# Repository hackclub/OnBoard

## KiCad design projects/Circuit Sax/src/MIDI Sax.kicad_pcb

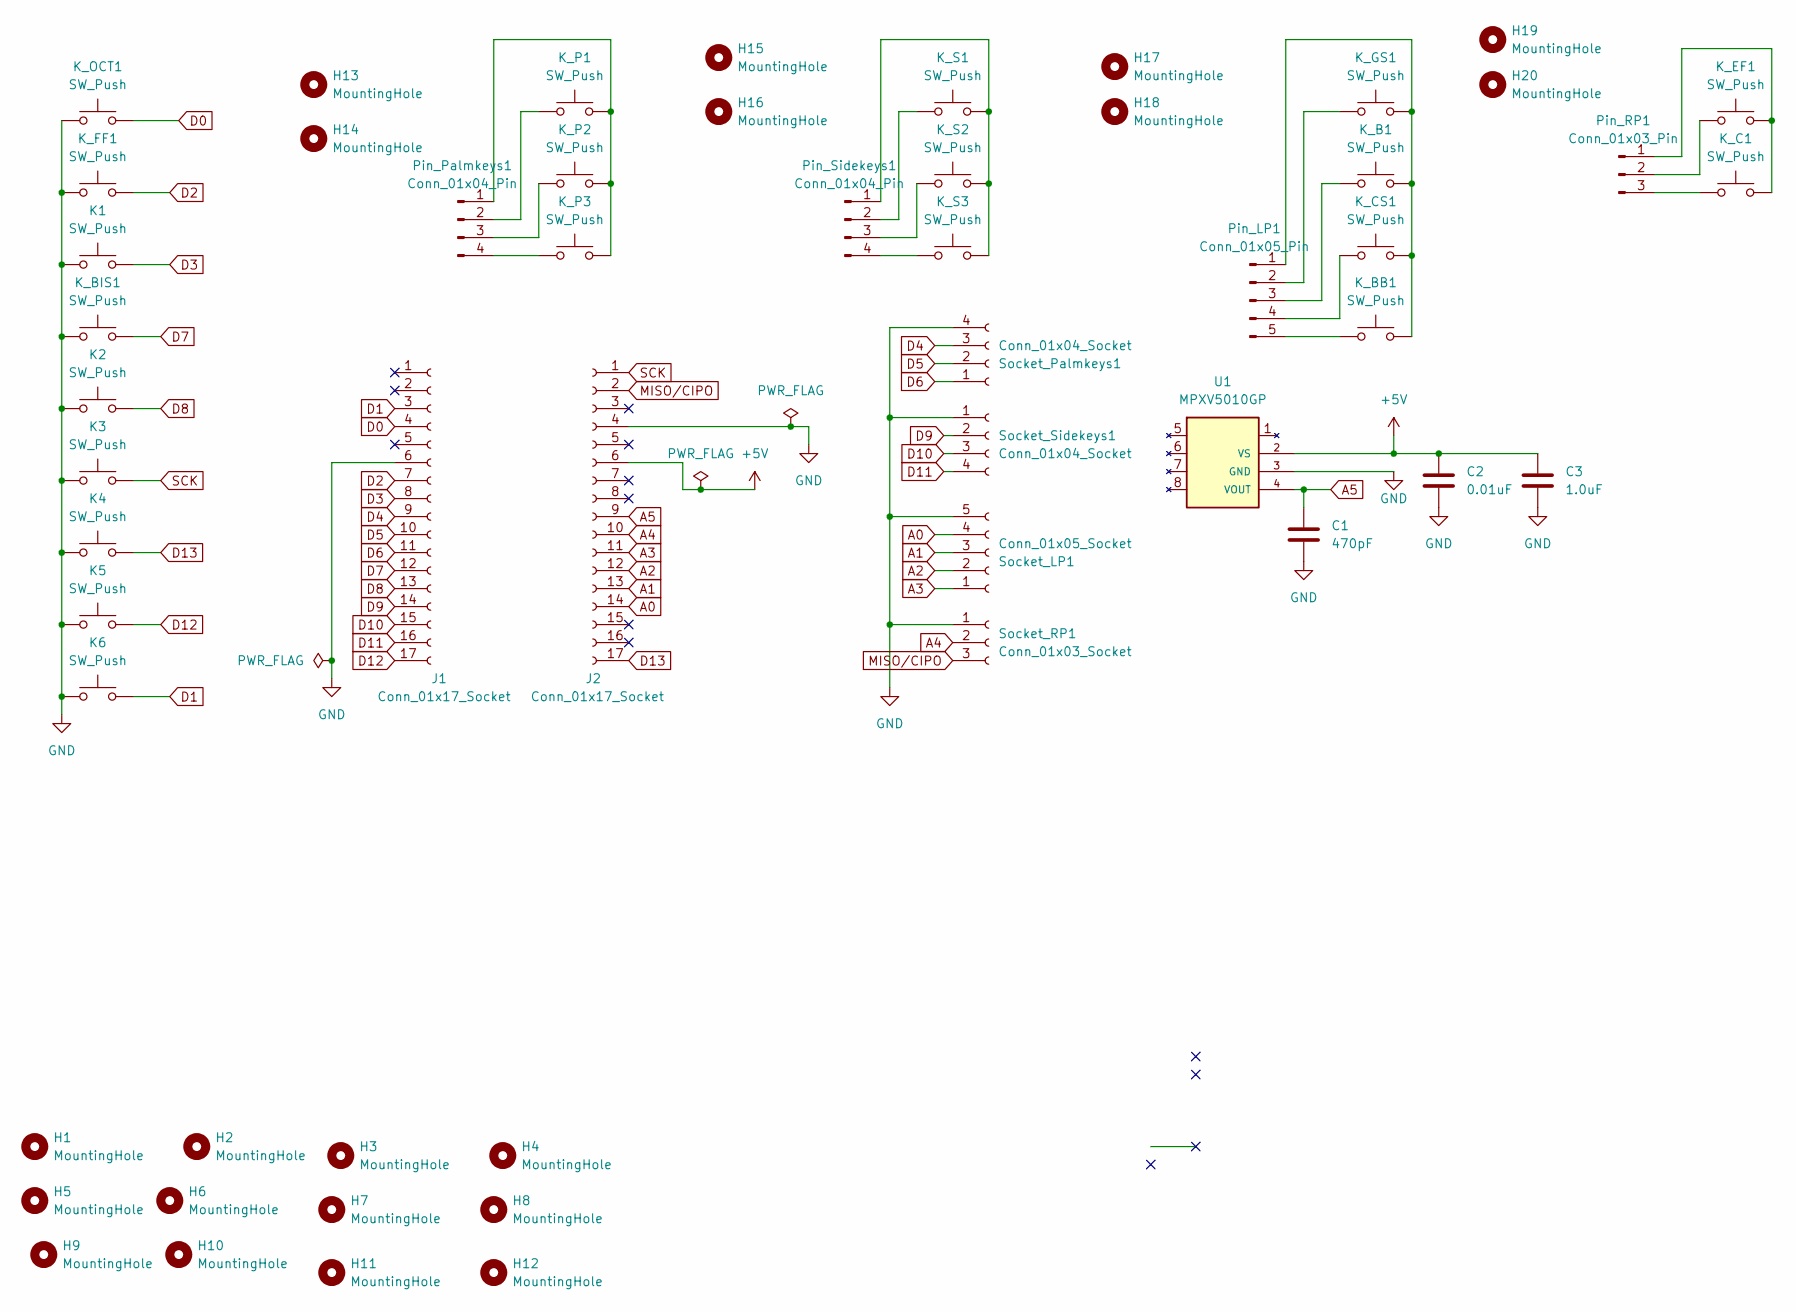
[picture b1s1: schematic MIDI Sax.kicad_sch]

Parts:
C1: 470pF; C_1206_3216Metric
C2: 0.01uF; C_1206_3216Metric
C3: 1.0uF; C_1206_3216Metric
H1, H2, H3, H4, H5, H6, H9, H10, H11, H12, H13, H14, H17, H18: MountingHole; MountingHole_2.85mm
H7, H8, H15, H16, H19, H20: MountingHole; MountingHole_3.3mm
J1, J2: Conn_01x17_Socket; PinSocket_1x17_P2.54mm_Vertical
K1, K2, K3, K4, K5, K6: SW_Push; SW_Cherry_MX_PCB
K_B1: SW_Push; SW_Cherry_MX_PCB
K_BB1: SW_Push; SW_Cherry_MX_PCB
K_BIS1: SW_Push; SW_Cherry_MX_PCB
K_C1: SW_Push; SW_Cherry_MX_PCB
K_CS1: SW_Push; SW_Cherry_MX_PCB
K_EF1: SW_Push; SW_Cherry_MX_PCB
K_FF1: SW_Push; SW_Cherry_MX_PCB
K_GS1: SW_Push; SW_Cherry_MX_PCB
K_OCT1: SW_Push; SW_Cherry_MX_PCB
K_P1, K_P2, K_P3: SW_Push; SW_Cherry_MX_PCB
K_S1, K_S2, K_S3: SW_Push; SW_Cherry_MX_PCB
Pin_LP1: Conn_01x05_Pin; SAMTEC_TSM-105-01-L-SH
Pin_Palmkeys1: Conn_01x04_Pin; PinHeader_1x04_P2.54mm_Vertical
Pin_RP1: Conn_01x03_Pin; CONN3_M20-8900_HRW
Pin_Sidekeys1: Conn_01x04_Pin; PinHeader_1x04_P2.54mm_Vertical
Socket_LP1: Conn_01x05_Socket; HARWIN_M20-7910542R
Socket_Palmkeys1: Conn_01x04_Socket; HARWIN_M20-7910442R
Socket_RP1: Conn_01x03_Socket; HARWIN_M20-7910342R
Socket_Sidekeys1: Conn_01x04_Socket; HARWIN_M20-7910442R
U1: MPXV5010GP; SOIC254P1821X762-8N

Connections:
+5V: C2.1, C3.1, J2.6, U1.2 (VS)
A0: J2.14, Socket_LP1.4
A1: J2.13, Socket_LP1.3
A2: J2.12, Socket_LP1.2
A3: J2.11, Socket_LP1.1
A4: J2.10, Socket_RP1.2
A5: C1.1, J2.9, U1.4 (VOUT)
D0: J1.4, K_OCT1.2
D1: J1.3, K6.2
D2: J1.7, K_FF1.2
D3: J1.8, K1.2
D4: J1.9, Socket_Palmkeys1.3
D5: J1.10, Socket_Palmkeys1.2
D6: J1.11, Socket_Palmkeys1.1
D7: J1.12, K_BIS1.2
D8: J1.13, K2.2
D9: J1.14, Socket_Sidekeys1.2
D10: J1.15, Socket_Sidekeys1.3
D11: J1.16, Socket_Sidekeys1.4
D12: J1.17, K5.2
D13: J2.17, K4.2
GND: C1.2, C2.2, C3.2, J1.6, J2.4, K1.1, K2.1, K3.1, K4.1, K5.1, K6.1, K_BIS1.1, K_FF1.1, K_OCT1.1, Socket_LP1.5, Socket_Palmkeys1.4, Socket_RP1.1, Socket_Sidekeys1.1, U1.3 (GND)
MISO/CIPO: J2.2, Socket_RP1.3
unnamed: K_B1.2, K_BB1.2, K_CS1.2, K_GS1.2, Pin_LP1.1
unnamed: K_GS1.1, Pin_LP1.2
unnamed: K_B1.1, Pin_LP1.3
unnamed: K_CS1.1, Pin_LP1.4
unnamed: K_BB1.1, Pin_LP1.5
unnamed: K_P1.2, K_P2.2, K_P3.2, Pin_Palmkeys1.1
unnamed: K_P1.1, Pin_Palmkeys1.2
unnamed: K_P2.1, Pin_Palmkeys1.3
unnamed: K_P3.1, Pin_Palmkeys1.4
unnamed: K_C1.2, K_EF1.2, Pin_RP1.1
unnamed: K_EF1.1, Pin_RP1.2
unnamed: K_C1.1, Pin_RP1.3
unnamed: K_S1.2, K_S2.2, K_S3.2, Pin_Sidekeys1.1
unnamed: K_S1.1, Pin_Sidekeys1.2
unnamed: K_S2.1, Pin_Sidekeys1.3
unnamed: K_S3.1, Pin_Sidekeys1.4
SCK: J2.1, K3.2

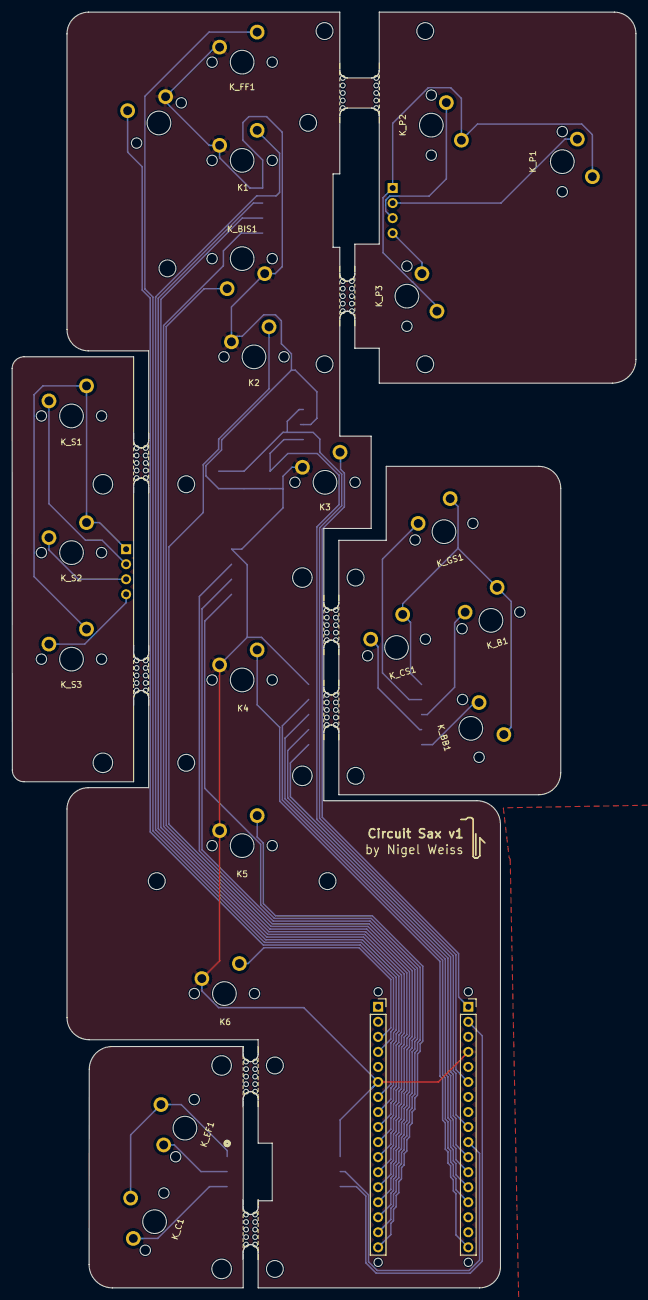
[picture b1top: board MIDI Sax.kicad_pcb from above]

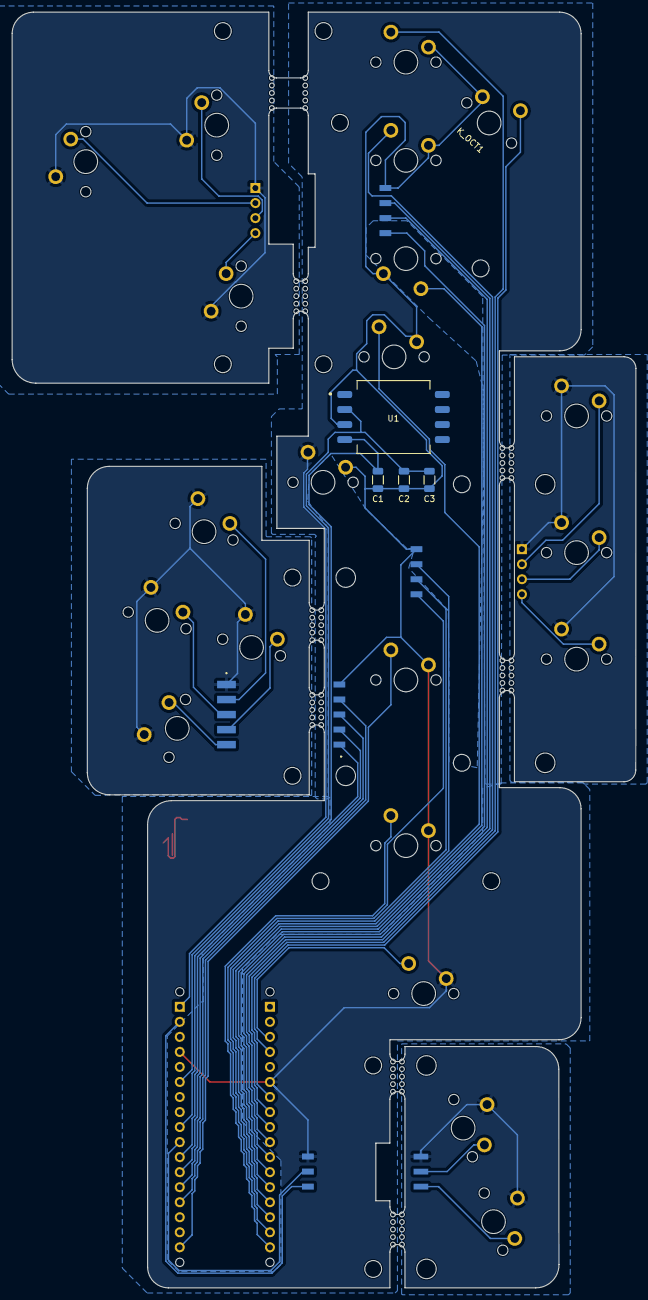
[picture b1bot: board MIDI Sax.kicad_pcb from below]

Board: 2 copper layers, 105.4 x 215.6 mm, 75 parts (13 on the bottom side), 40 nets.

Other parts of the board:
H1#2, H1#3, H1#4, H1#5: MountingHole; MountingHole_1.4mm
TAB4, TAB4#2, TAB4#3, TAB4#4, TAB4#5, TAB4#6, TAB4#7, TAB4#8, TAB4#9, TAB4#10, TAB4#11, TAB4#12, TAB4#13, TAB4#14, TAB4#15, TAB4#16: Mouse Bites; Breakout tab

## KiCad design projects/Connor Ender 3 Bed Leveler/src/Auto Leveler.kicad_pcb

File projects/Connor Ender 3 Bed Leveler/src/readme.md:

# Design files
#### These are all the files that have the designs in them

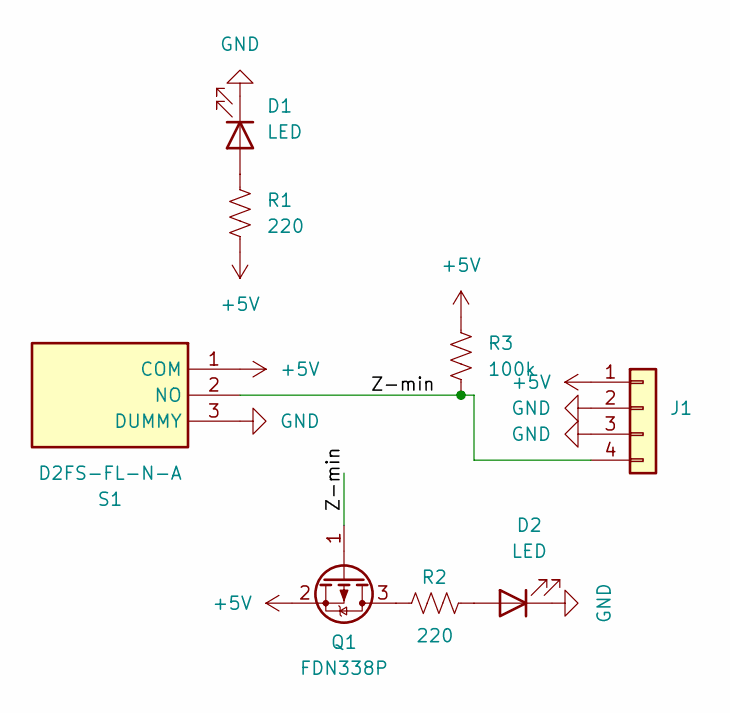
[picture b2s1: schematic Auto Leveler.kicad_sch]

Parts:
D1, D2: LED; LED_D3.0mm
J1: 502386-0470; 26448034; Mouser Part Number 538-502386-0470
Q1: FDN338P; SOT-23
R1, R2: 220; R_0805_2012Metric_Pad1.20x1.40mm_HandSolder
R3: 100k; R_0805_2012Metric_Pad1.20x1.40mm_HandSolder
S1: D2FS-FL-N-A; D2FSFLNA; Manufacturer_Part_Number D2FS-FL-N-A; Mouser Part Number 653-D2FS-FL-N-A

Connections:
+5V: J1.1, Q1.2 (S), R1.2, R3.1, S1.1 (COM)
/Z-min: J1.4, Q1.1 (G), R3.2, S1.2 (NO)
GND: D1.1 (K), D2.1 (K), J1.2, J1.3, S1.3 (DUMMY)
unnamed: D1.2 (A), R1.1
unnamed: D2.2 (A), R2.2
unnamed: Q1.3 (D), R2.1

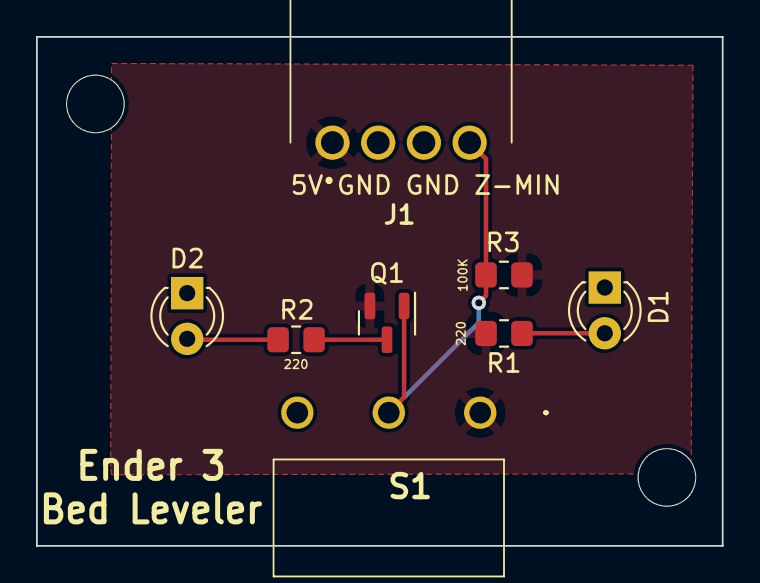
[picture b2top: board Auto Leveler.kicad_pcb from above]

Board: 2 copper layers, 38.1 x 28.3 mm, 8 parts (0 on the bottom side), 6 nets.

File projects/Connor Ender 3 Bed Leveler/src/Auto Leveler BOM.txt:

Ref	Quant	Description		Digikey pt#
D1,D2	  2	3 mm LED		Just a normal LED
R1,R2	  2	220 0805 RES		RC0805FR-13220RL
R3	  1	100K 0805 RES		AC0805FR-7W100KL
J1	  1	4 POS R/A CONN		2-644803-4<--get this?
Q1	  1	MOSFET P-channel	FDN338P
S1	  1	NO Lever Limit Switch	D2SF-FL-N-A

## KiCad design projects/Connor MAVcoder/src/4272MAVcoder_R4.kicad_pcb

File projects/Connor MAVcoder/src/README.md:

## What Are all these files???
Inside the folder there are all of the gbr files, along with the schematic, pcb board layout, and the main software for the design.

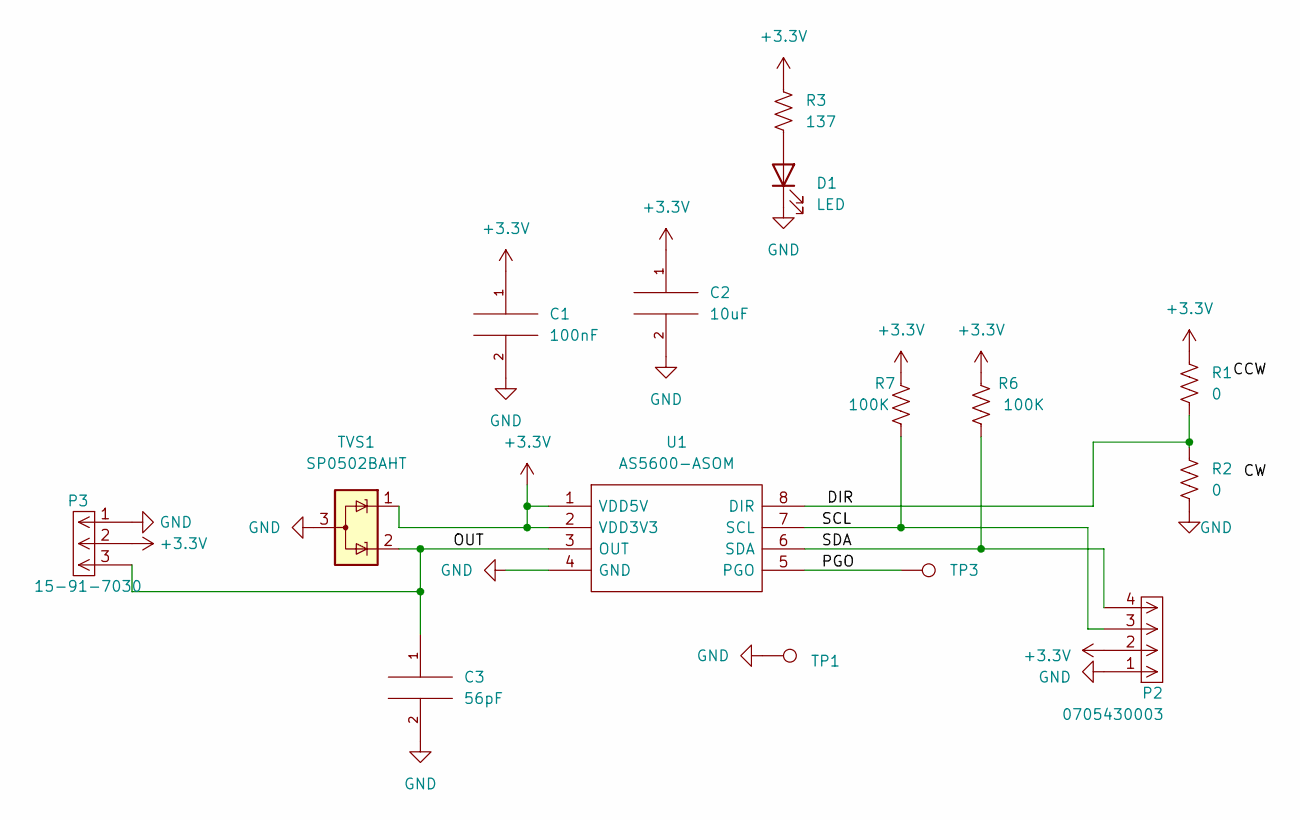
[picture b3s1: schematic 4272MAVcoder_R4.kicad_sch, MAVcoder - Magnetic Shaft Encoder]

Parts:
C1: 100nF; C_0603_1608Metric_Pad1.08x0.95mm_HandSolder
C2: 10uF; C_0805_2012Metric_Pad1.18x1.45mm_HandSolder
C3: 56pF; C_0603_1608Metric_Pad1.08x0.95mm_HandSolder
D1: LED; LED_D3.0mm
P2: 0705430003; Molex_SL_171971-0004_1x04_P2.54mm_Vertical; Manufacturer_Part_Number 0015912045; Mouser Part Number N/A
P3: 15-91-7030; 705550037; Mouser Part Number 538-15-91-7030
R1, R2: 0; R_0603_1608Metric_Pad0.98x0.95mm_HandSolder
R3: 137; R_0603_1608Metric_Pad0.98x0.95mm_HandSolder
R6, R7: 100K; R_0603_1608Metric_Pad0.98x0.95mm_HandSolder
TP1, TP3: TestPoint; TestPoint_THTPad_1.0x1.0mm_Drill0.5mm
TVS1: SP0502BAHT; SOT-23
U1: AS5600-ASOM; SOIC-8_3.9x4.9mm_P1.27mm; Mouser Part Number 985-AS5600-ASOM

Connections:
+3.3V: C1.1, C2.1, P2.2, R1.1, R3.1, R6.2, R7.2, TVS1.1 (K), U1.1 (VDD5V), U1.2 (VDD3V3); also elsewhere on the board
/DIR: R1.2, R2.1, U1.8 (DIR)
/OUT: C3.1, TVS1.2 (K), U1.3 (OUT); also elsewhere on the board
/PGO: TP3.1, U1.5 (PGO)
/SCL: P2.3, R7.1, U1.7 (SCL)
/SDA: P2.4, R6.1, U1.6 (SDA)
GND: C1.2, C2.2, C3.2, D1.1 (K), P2.1, R2.2, TP1.1, TVS1.3 (A), U1.4 (GND); also elsewhere on the board
unnamed: D1.2 (A), R3.2

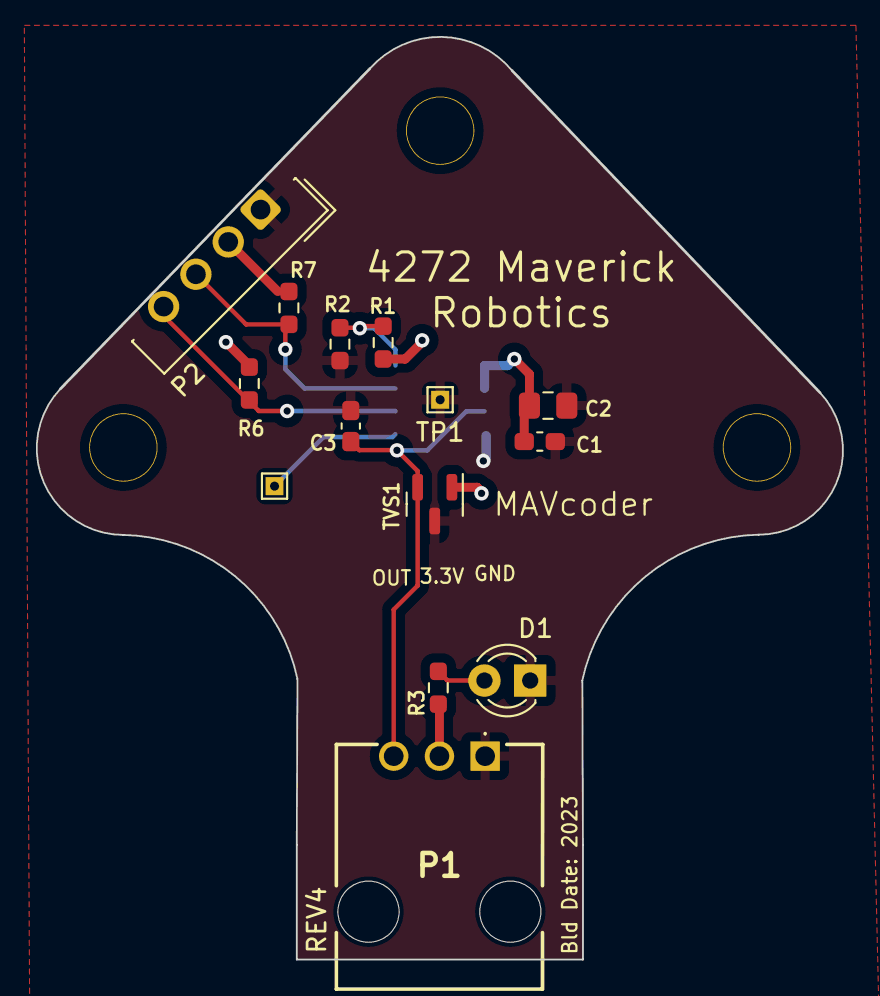
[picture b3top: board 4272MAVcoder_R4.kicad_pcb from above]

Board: 2 copper layers, 44.8 x 51.3 mm, 15 parts (1 on the bottom side), 8 nets.

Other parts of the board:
P1: 15-91-7030; 705550037

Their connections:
+3.3V: P1.2; also elsewhere on the board
/OUT: P1.3; also elsewhere on the board
GND: P1.1; also elsewhere on the board

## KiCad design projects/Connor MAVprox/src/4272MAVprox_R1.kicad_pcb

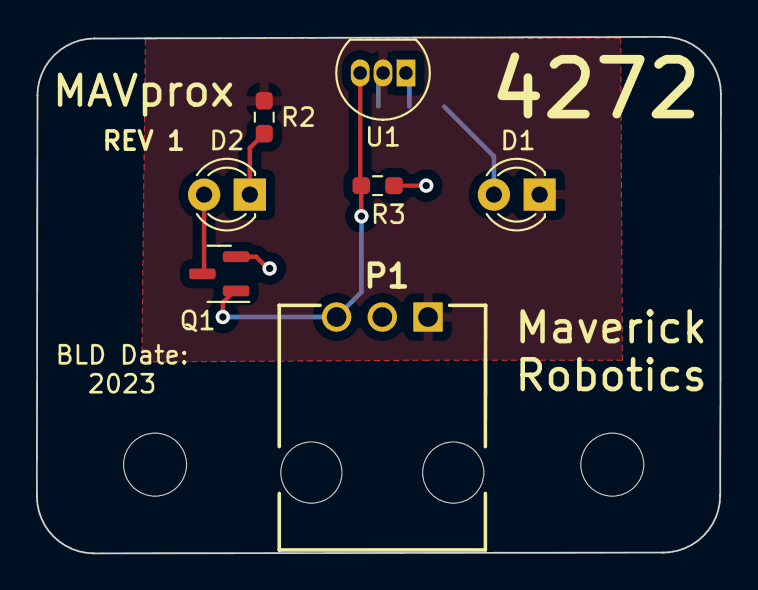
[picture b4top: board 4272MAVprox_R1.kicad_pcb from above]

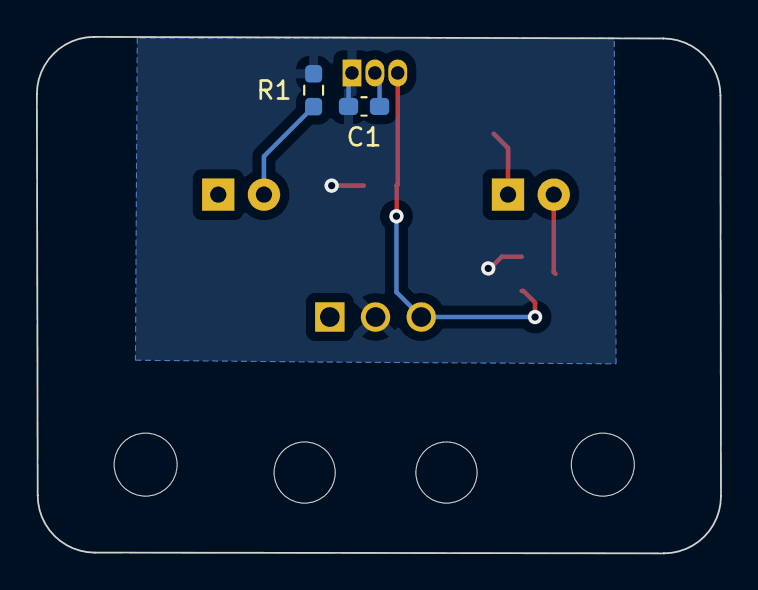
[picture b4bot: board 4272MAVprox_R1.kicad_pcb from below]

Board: 2 copper layers, 38.0 x 28.7 mm, 9 parts (2 on the bottom side), 6 nets.

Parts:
C1: 100nF; C_0603_1608Metric_Pad1.08x0.95mm_HandSolder
D1, D2: LED; LED_D3.0mm
P1: 15-91-7030; 705550037
Q1: FDN340P; SOT-23
R1, R2: 137; R_0603_1608Metric_Pad0.98x0.95mm_HandSolder
R3: 100K; R_0603_1608Metric_Pad0.98x0.95mm_HandSolder
U1: DRV5033FAxLPG; TO-92_Inline

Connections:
+3.3V: C1.1, P1.2, Q1.2 (S), R1.1, R3.2, U1.1 (VCC)
GND: C1.2, D1.1 (K), P1.1, R2.2, U1.2 (GND)
unnamed: D1.2 (A), R1.2
unnamed: D2.2 (A), Q1.3 (D)
unnamed: D2.1 (K), R2.1
unnamed: P1.3, Q1.1 (G), R3.1, U1.3 (OUT)

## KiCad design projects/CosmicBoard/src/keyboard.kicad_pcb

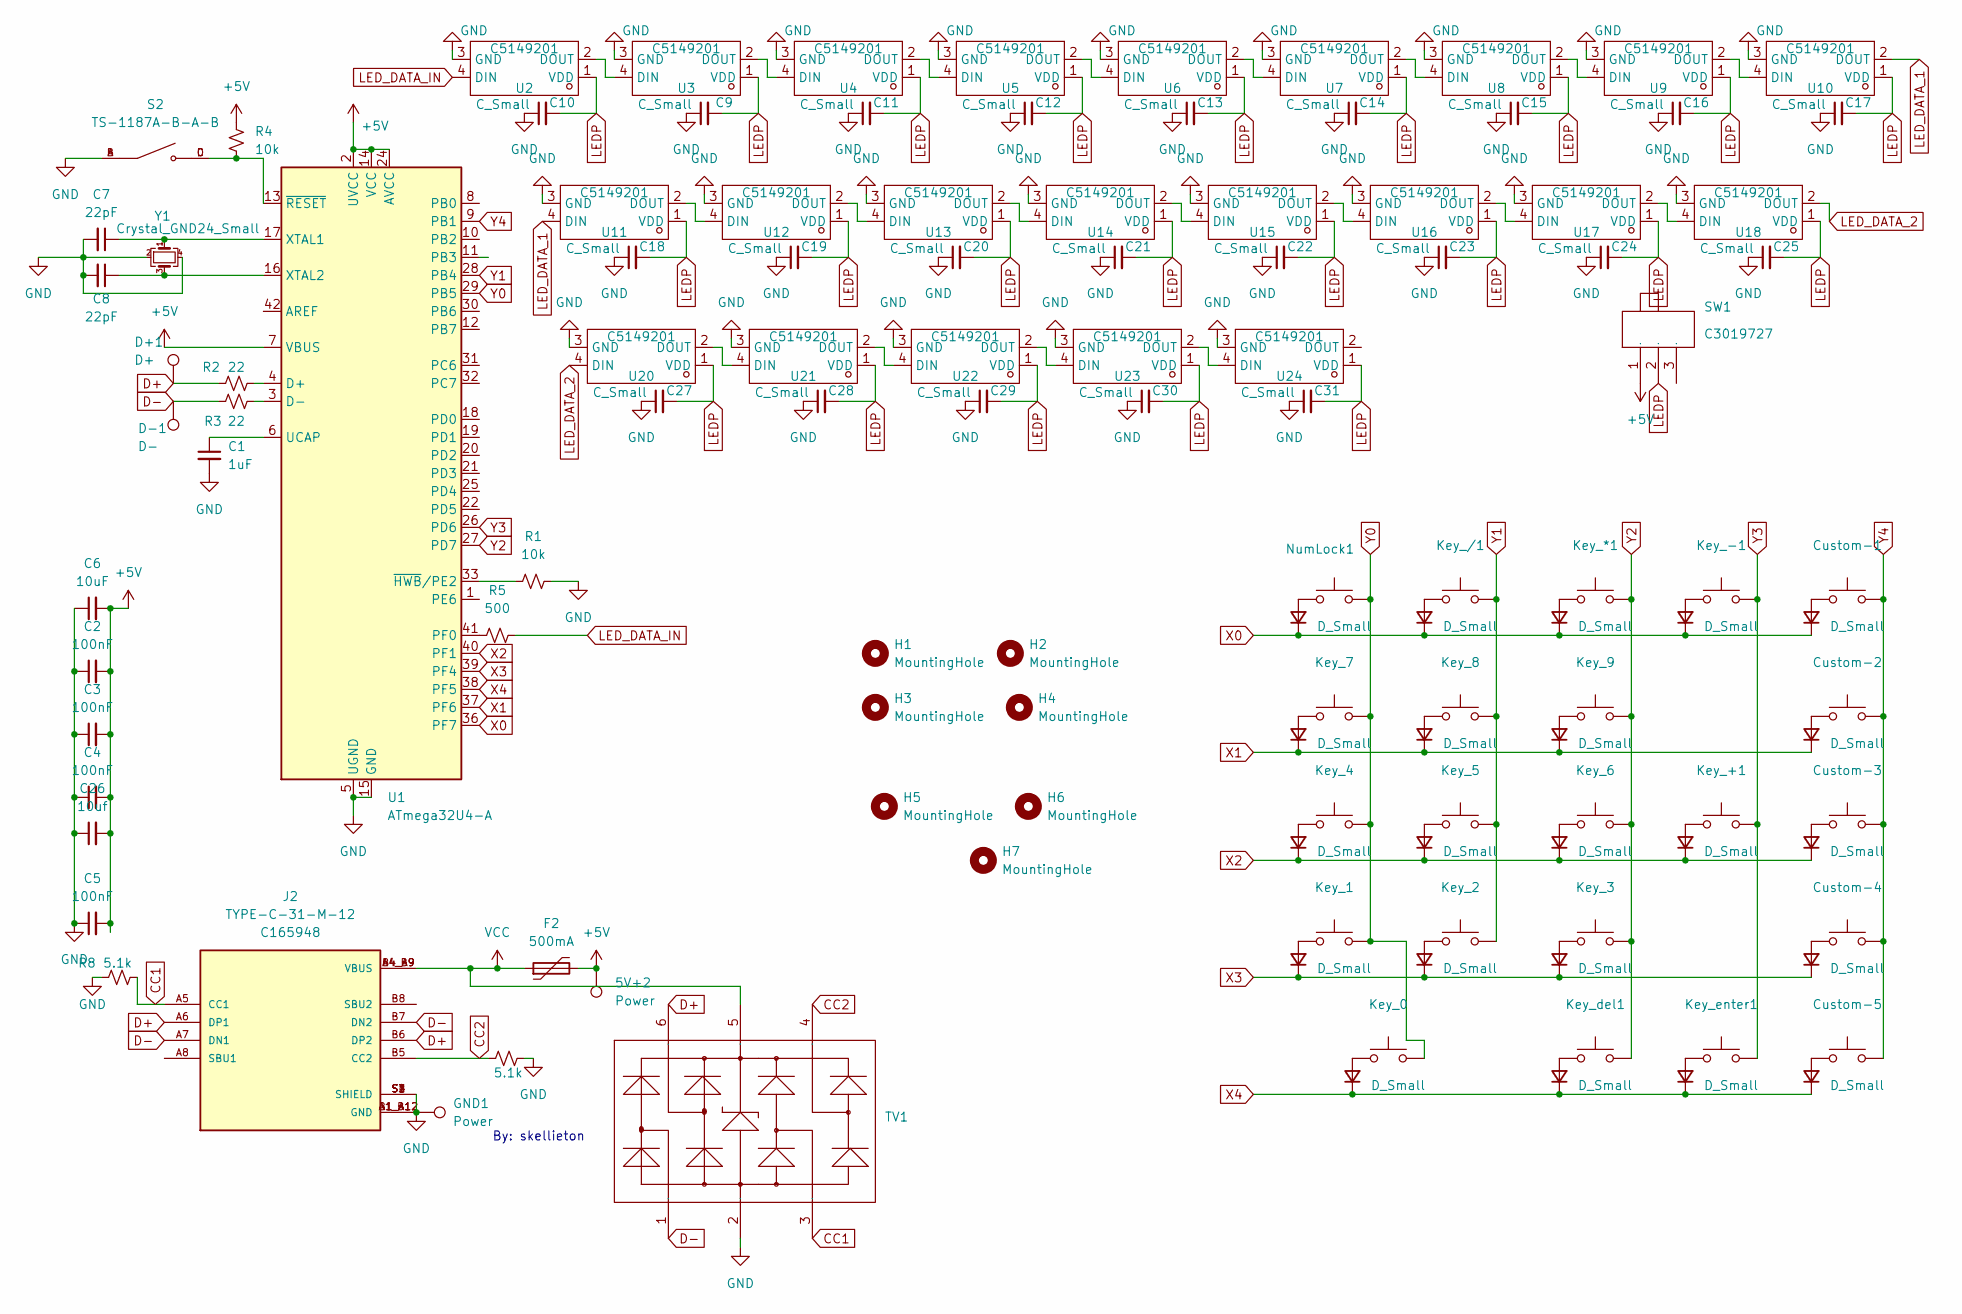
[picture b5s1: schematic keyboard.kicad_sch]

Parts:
5V+2: Power; TestPoint_Pad_1.0x1.0mm
C1: 1uF; C_0805_2012Metric; LCSC C28323
C2, C3, C4: 100nF; C_0805_2012Metric; LCSC C49678
C5: 100nF; C_0805_2012Metric
C6: 10uF; C_0805_2012Metric; LCSC C15850
C7: 22pF; C_0805_2012Metric; LCSC C1804
C8: 22pF; C_0805_2012Metric
C9, C11, C12, C13, C14, C15, C16, C17, C18, C19, C20, C21, C22, C23, C24, C25, C27, C28, C29, C30, C31: C_Small; C_0805_2012Metric
C10: C_Small; C_0805_2012Metric; LCSC C49678
C26: 10uf; C_0805_2012Metric; LCSC C15850
Custom-1, Custom-2, Custom-3, Custom-4, Custom-5: SW_Push; SW_MX_HS_S_CPG151101S11_1u
D1, D2: D_Small; D_SOD-123; LCSC C64898
D3, D4, D5, D6, D7, D8, D9, D10, D11, D12, D13, D14, D16, D17, D18, D19, D20, D21, D23, D25: D_Small; D_SOD-123
D+1: D+; TestPoint_Pad_1.0x1.0mm
D-1: D-; TestPoint_Pad_1.0x1.0mm
F2: 500mA; Fuse_1206_3216Metric; LCSC C70076
GND1: Power; TestPoint_Pad_1.0x1.0mm
H1, H2, H3, H4: MountingHole; MountingHole_3.2mm_M3
H5, H6, H7: MountingHole; STAB_MX_2u
J2: TYPE-C-31-M-12; HRO_TYPE-C-31-M-12; LCSC C165948
Key_0: SW_Push_U2; SW_MX_HS_S_CPG151101S11_1u
Key_1, Key_2, Key_3, Key_4, Key_5, Key_6, Key_7, Key_8, Key_9: SW_Push; SW_MX_HS_S_CPG151101S11_1u
Key_*1: SW_Push; SW_MX_HS_S_CPG151101S11_1u
Key_+1: SW_Push_U2; SW_MX_HS_S_CPG151101S11_1u
Key_-1: SW_Push; SW_MX_HS_S_CPG151101S11_1u
Key_/1: SW_Push; SW_MX_HS_S_CPG151101S11_1u
Key_del1: SW_Push; SW_MX_HS_S_CPG151101S11_1u
Key_enter1: SW_Push_U2; SW_MX_HS_S_CPG151101S11_1u
NumLock1: SW_Push; SW_MX_HS_S_CPG151101S11_1u; LCSC C41430893
R1, R4: 10k; R_0805_2012Metric; LCSC C17414
R2, R3: 22; R_0805_2012Metric; LCSC C17561
R5: 500; R_0805_2012Metric
R7, R8: 5.1k; R_0805_2012Metric; LCSC C27834
S2: TS-1187A-B-A-B; SW_TS-1187A-B-A-B
SW1: SW-TH_MK-12D18-G040; Manufacturer Part MK-12D18-G020; LCSC Part Name 边三脚微型拨动开关G4
TV1: SOT-23-6_L2.9-W1.6-P0.95-LS2.8-BR; Manufacturer Part SRV05-4-P-T7; LCSC Part Name SRV05-4-P-T7
U1: ATmega32U4-A; TQFP-44_10x10mm_P0.8mm
U2, U3, U4, U5, U6, U12, U13, U14, U15, U22, U23, U24: MX-SK-E-Left_Right; Manufacturer Part SK6812MINI-E; LCSC Part Name SK6812MINI-E
U7, U8, U9, U10, U11, U16, U17, U18, U20, U21: MX-SK-E-Right_Left; Manufacturer Part SK6812MINI-E; LCSC Part Name SK6812MINI-E
Y1: Crystal_GND24_Small; Crystal_SMD_3225-4Pin_3.2x2.5mm; LCSC C13738

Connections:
+5V: 5V+2.1, C2.2, C3.2, C4.2, C5.2, C6.2, C26.2, F2.2, R4.1, SW1.1, U1.2 (UVCC), U1.7 (VBUS), U1.14 (VCC), U1.24 (AVCC), U1.34 (VCC), U1.44 (AVCC)
CC1: J2.A5 (CC1), R8.2, TV1.3
CC2: J2.B5 (CC2), R7.2, TV1.4
D+: D+1.1, J2.A6 (DP1), J2.B6 (DP2), R2.2, TV1.6
D-: D-1.1, J2.A7 (DN1), J2.B7 (DN2), R3.1, TV1.1
GND: C1.2, C2.1, C3.1, C4.1, C5.1, C6.1, C7.2, C8.2, C9.1, C10.1, C11.1, C12.1, C13.1, C14.1, C15.1, C16.1, C17.1, C18.1, C19.1, C20.1, C21.1, C22.1, C23.1, C24.1, C25.1, C26.1, C27.1, C28.1, C29.1, C30.1, C31.1, GND1.1, J2.A1_B12 (GND), J2.B1_A12 (GND), J2.S1 (SHIELD), J2.S2 (SHIELD), J2.S3 (SHIELD), J2.S4 (SHIELD), R1.2, R7.1, R8.1, S2.A, S2.B, TV1.2, U1.5 (UGND), U1.15 (GND), U1.23 (GND), U1.35 (GND), U1.43 (GND), U2.3 (GND), U3.3 (GND), U4.3 (GND), U5.3 (GND), U6.3 (GND), U7.3 (GND), U8.3 (GND), U9.3 (GND), U10.3 (GND), U11.3 (GND), U12.3 (GND), U13.3 (GND), U14.3 (GND), U15.3 (GND), U16.3 (GND), U17.3 (GND), U18.3 (GND), U20.3 (GND), U21.3 (GND), U22.3 (GND), U23.3 (GND), U24.3 (GND), Y1.2, Y1.4
LEDP: C9.2, C10.2, C11.2, C12.2, C13.2, C14.2, C15.2, C16.2, C17.2, C18.2, C19.2, C20.2, C21.2, C22.2, C23.2, C24.2, C25.2, C27.2, C28.2, C29.2, C30.2, C31.2, SW1.2, U2.1 (VDD), U3.1 (VDD), U4.1 (VDD), U5.1 (VDD), U6.1 (VDD), U7.1 (VDD), U8.1 (VDD), U9.1 (VDD), U10.1 (VDD), U11.1 (VDD), U12.1 (VDD), U13.1 (VDD), U14.1 (VDD), U15.1 (VDD), U16.1 (VDD), U17.1 (VDD), U18.1 (VDD), U20.1 (VDD), U21.1 (VDD), U22.1 (VDD), U23.1 (VDD), U24.1 (VDD)
LED_DATA_1: U10.2 (DOUT), U11.4 (DIN)
LED_DATA_2: U18.2 (DOUT), U20.4 (DIN)
LED_DATA_IN: R5.2, U2.4 (DIN)
unnamed: D1.2 (A), NumLock1.1
unnamed: D2.2 (A), Key_/1.1
unnamed: D3.2 (A), Key_7.1
unnamed: D4.2 (A), Key_8.1
unnamed: D5.2 (A), Key_4.1
unnamed: D6.2 (A), Key_1.1
unnamed: D7.2 (A), Key_5.1
unnamed: D8.2 (A), Key_2.1
unnamed: D9.2 (A), Key_*1.1
unnamed: D10.2 (A), Key_9.1
unnamed: D11.2 (A), Key_-1.1
unnamed: D12.2 (A), Key_+1.1
unnamed: D13.2 (A), Key_6.1
unnamed: D14.2 (A), Key_3.1
unnamed: D16.2 (A), Key_enter1.1
unnamed: Custom-1.1, D17.2 (A)
unnamed: Custom-2.1, D18.2 (A)
unnamed: Custom-3.1, D19.2 (A)
unnamed: Custom-4.1, D20.2 (A)
unnamed: D21.2 (A), Key_0.1
unnamed: D23.2 (A), Key_del1.1
unnamed: Custom-5.1, D25.2 (A)
unnamed: R2.1, U1.4 (D+)
unnamed: R3.2, U1.3 (D-)
unnamed: R5.1, U1.41 (PF0)
unnamed: C1.1, U1.6 (UCAP)
unnamed: C7.1, U1.17 (XTAL1), Y1.1
unnamed: C8.1, U1.16 (XTAL2), Y1.3
unnamed: R1.1, U1.33 (~HWB/PE2)
unnamed: R4.2, S2.C, S2.D, U1.13 (~RESET)
unnamed: U2.2 (DOUT), U3.4 (DIN)
unnamed: U3.2 (DOUT), U4.4 (DIN)
unnamed: U4.2 (DOUT), U5.4 (DIN)
unnamed: U5.2 (DOUT), U6.4 (DIN)
unnamed: U6.2 (DOUT), U7.4 (DIN)
unnamed: U7.2 (DOUT), U8.4 (DIN)
unnamed: U8.2 (DOUT), U9.4 (DIN)
unnamed: U9.2 (DOUT), U10.4 (DIN)
unnamed: U11.2 (DOUT), U12.4 (DIN)
unnamed: U12.2 (DOUT), U13.4 (DIN)
unnamed: U13.2 (DOUT), U14.4 (DIN)
unnamed: U14.2 (DOUT), U15.4 (DIN)
unnamed: U15.2 (DOUT), U16.4 (DIN)
unnamed: U16.2 (DOUT), U17.4 (DIN)
unnamed: U17.2 (DOUT), U18.4 (DIN)
unnamed: U20.2 (DOUT), U21.4 (DIN)
unnamed: U21.2 (DOUT), U22.4 (DIN)
unnamed: U22.2 (DOUT), U23.4 (DIN)
unnamed: U23.2 (DOUT), U24.4 (DIN)
VCC: F2.1, J2.A4_B9 (VBUS), J2.B4_A9 (VBUS), TV1.5
X0: D1.1 (K), D2.1 (K), D9.1 (K), D11.1 (K), D17.1 (K), U1.36 (PF7)
X1: D3.1 (K), D4.1 (K), D10.1 (K), D18.1 (K), U1.37 (PF6)
X2: D5.1 (K), D7.1 (K), D12.1 (K), D13.1 (K), D19.1 (K), U1.40 (PF1)
X3: D6.1 (K), D8.1 (K), D14.1 (K), D20.1 (K), U1.39 (PF4)
X4: D16.1 (K), D21.1 (K), D23.1 (K), D25.1 (K), U1.38 (PF5)
Y0: Key_0.2, Key_1.2, Key_4.2, Key_7.2, NumLock1.2, U1.29 (PB5)
Y1: Key_2.2, Key_5.2, Key_8.2, Key_/1.2, U1.28 (PB4)
Y2: Key_3.2, Key_6.2, Key_9.2, Key_*1.2, Key_del1.2, U1.27 (PD7)
Y3: Key_+1.2, Key_-1.2, Key_enter1.2, U1.26 (PD6)
Y4: Custom-1.2, Custom-2.2, Custom-3.2, Custom-4.2, Custom-5.2, U1.9 (PB1)

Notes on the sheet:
By: skellieton

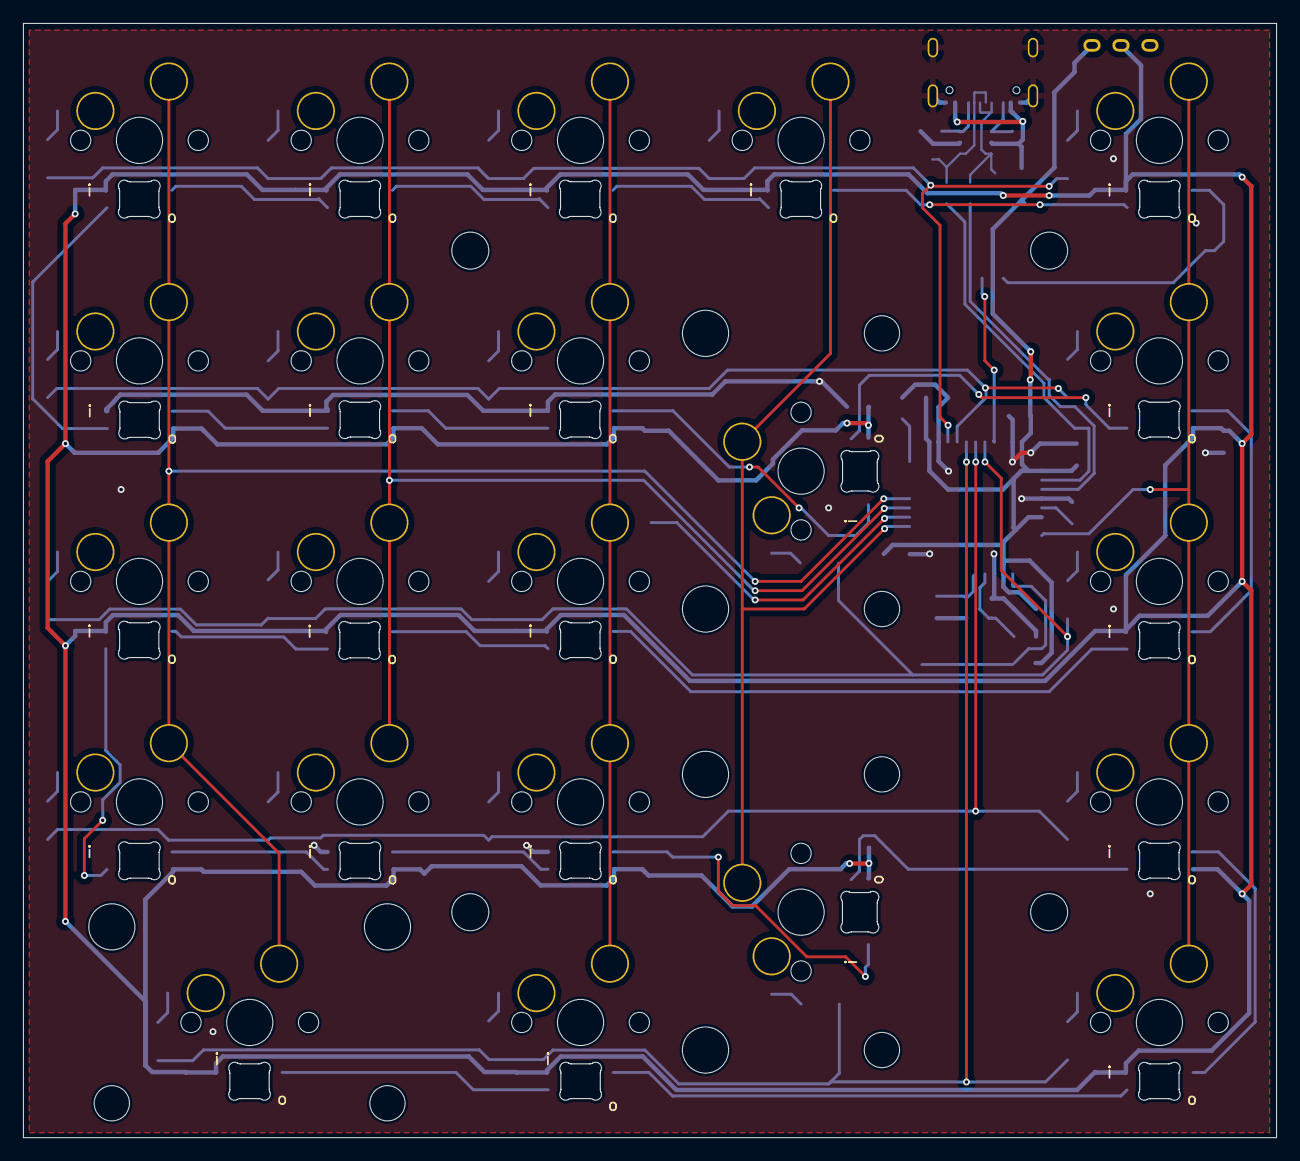
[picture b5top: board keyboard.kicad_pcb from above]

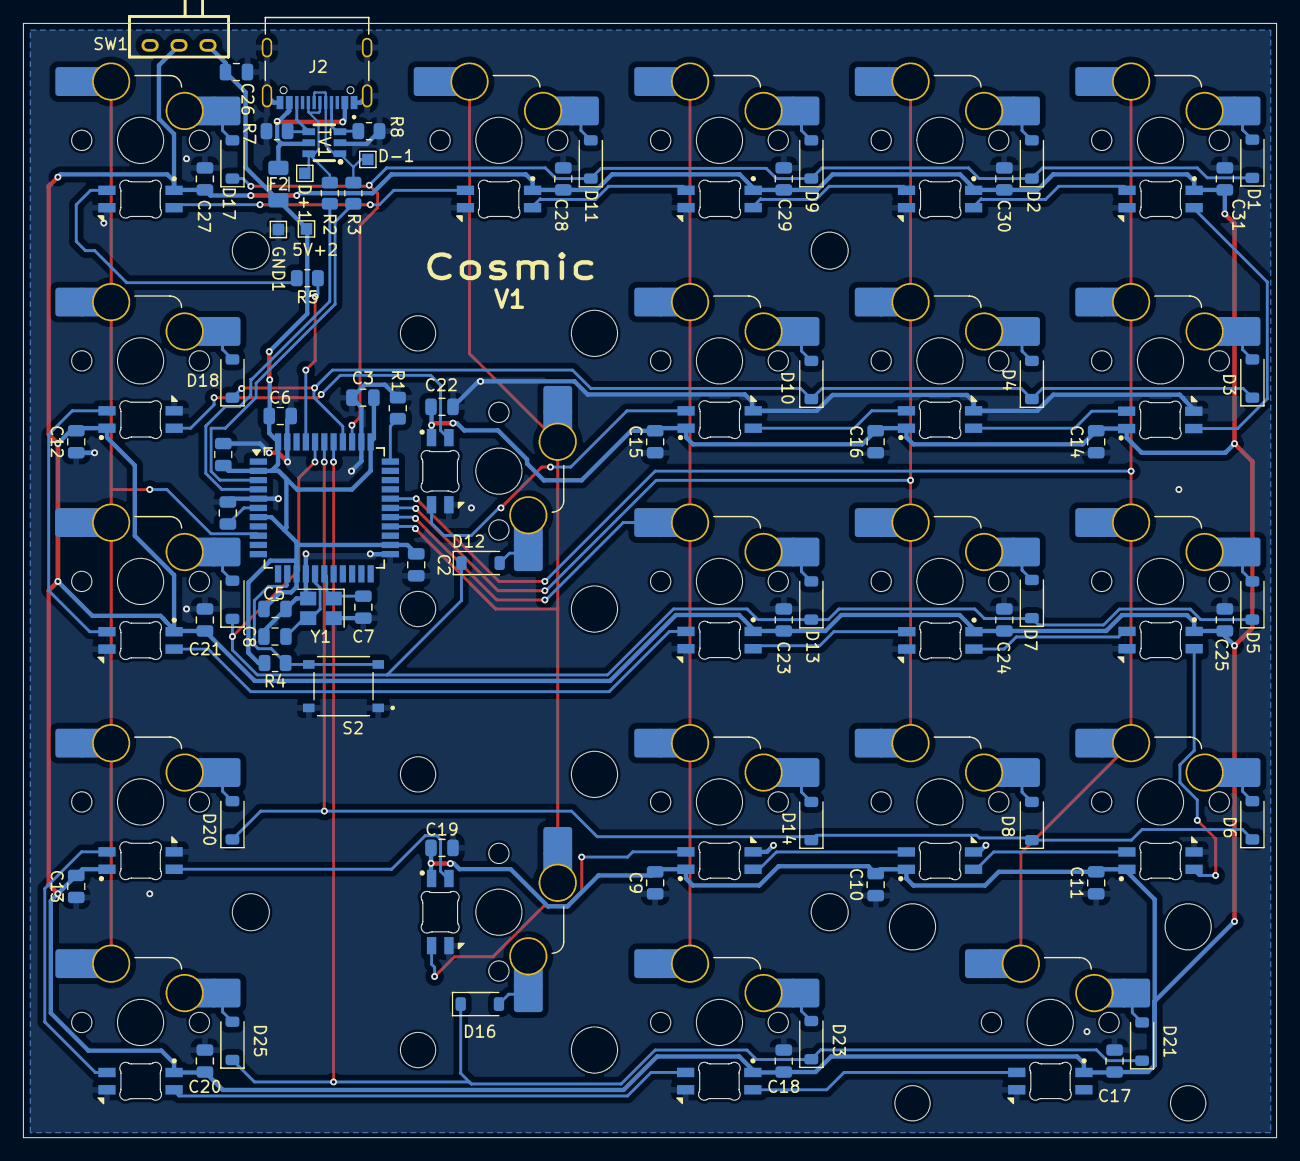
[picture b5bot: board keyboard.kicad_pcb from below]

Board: 2 copper layers, 108.2 x 96.2 mm, 122 parts (115 on the bottom side), 70 nets.

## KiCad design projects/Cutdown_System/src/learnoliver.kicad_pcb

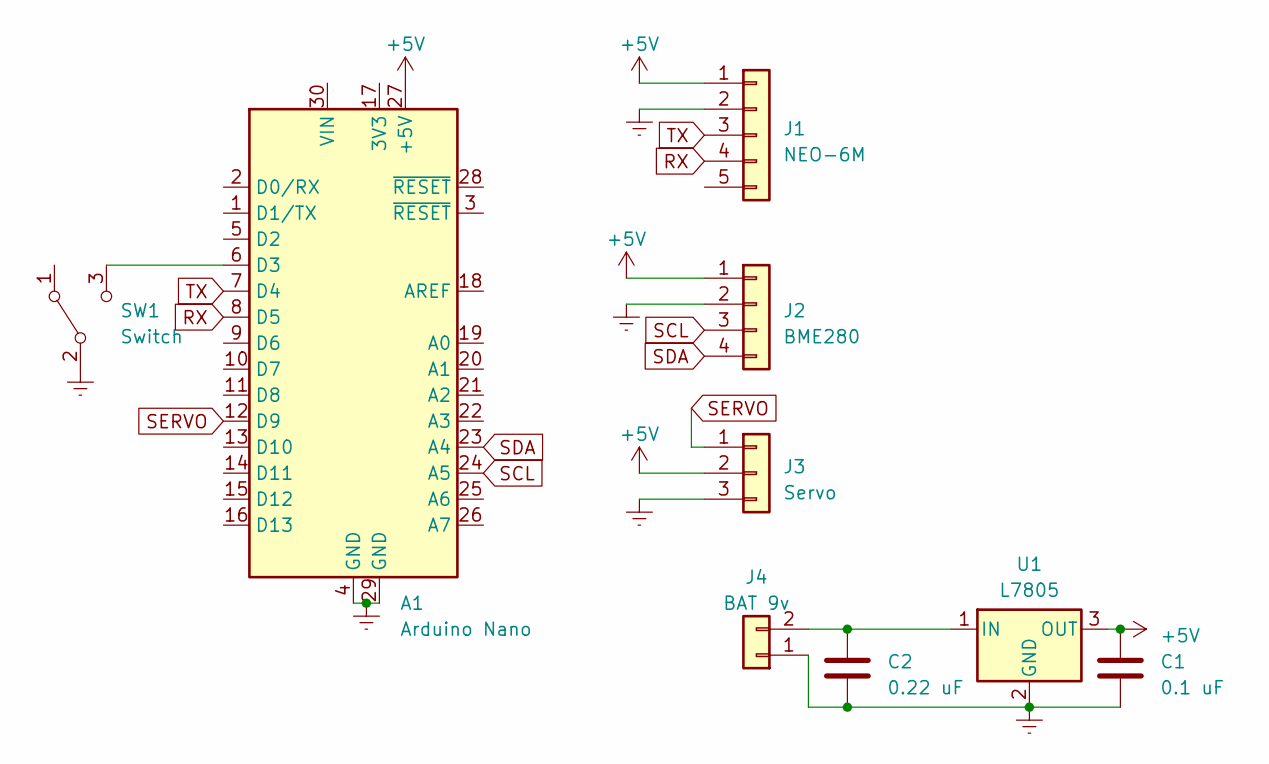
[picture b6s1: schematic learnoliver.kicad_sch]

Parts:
A1: Arduino Nano; Arduino_Nano
C1: 0.1 uF; C_Disc_D4.7mm_W2.5mm_P5.00mm
C2: 0.22 uF; C_Disc_D4.7mm_W2.5mm_P5.00mm
J1: NEO-6M; PinHeader_1x05_P2.54mm_Vertical
J2: BME280; PinHeader_1x04_P2.54mm_Vertical
J3: Servo; PinHeader_1x03_P2.54mm_Vertical
J4: BAT 9v; PinHeader_1x02_P2.54mm_Vertical
SW1: Switch; PinHeader_1x03_P2.54mm_Vertical
U1: L7805; TO-220-3_Vertical

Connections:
+5V: A1.27 (+5V), C1.1, J1.1, J2.1, J3.2, U1.3 (OUT)
Earth: A1.4 (GND), A1.29 (GND), C1.2, C2.2, J1.2, J2.2, J3.3, J4.1, SW1.2 (B), U1.2 (GND)
unnamed: A1.6 (D3), SW1.3 (C)
unnamed: C2.1, J4.2, U1.1 (IN)
RX: A1.8 (D5), J1.4
SCL: A1.24 (A5), J2.3
SDA: A1.23 (A4), J2.4
SERVO: A1.12 (D9), J3.1
TX: A1.7 (D4), J1.3
